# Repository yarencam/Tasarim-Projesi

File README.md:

# Damla Sulama Sistemi Kontrol Kartı
Proje kapsamında, el ile kontrol edilen, bir dizel motor vasıtasıyla sisteme su basan, eski tip **_Damla Sulama Sistemi_** kısmen modernize edilerek arıza ve su kesilmelerinde sistemi durdurarak kullanıcıyı bilgilendirecek yetenekler eklenecektir.

Bitki sulama ve sulamanın otomatik başlatılması için gerekli ölçüm ve kontroller bu projenin kapsamı dışındadır. Bahsi geçen yetenekler sonraki versiyonlarda sisteme eklenebilir.

## Damla Sulama Sistemi
Damla sulama, toprak yüzeyine veya yüzeyin hemen altına yerleştirilen küçük çaplı orifis yardımıyla arıtılmış suyu toprak yüzeyine veya içerisine veren bir sistemdir. Bu sistem suyun belirlenmiş bir desene alçak basınç altında verilmesine imkan sağlar. Bu sistemde su yaygın boru ağı aracılığı ile her bitkiye kadar götürülür. Öte yandan bitkilere verilecek gübreler de sulama suyu ile birlikte verilebilir (fertigation). Kısaca sistemin esası bitkinin ihtiyaç duyduğu su ve besin maddesi miktarını optimum seviyede tutmaktır. Bu yöntem sera, meyve, sebze bahçelerinde en çok kullanılan ve ekonomik su kullanımı sağlayan bir yöntemdir.

Damla sulama sistemleri genellikle aşağıdaki parçalardan oluşur;

* Sisteme su sağlayan basınçlı bir tank
* Tankı doldurmak ve yeterli basıncı sağlamak için bir pompa
* Pompaya hareket sağlamak için bir motor
* Sisteme su sağlamak için bir su kaynağı (su deposu veya sulama kanalı)

## Damla Sulama Sistemlerinde Çozülmesi Amaçlanan Sorun
Bu tip sistemlerde çoğunlukla bir elektrik motoru tercih edilse de eski sistemlerde veya elektrik olmayan bölgelerde halen dizel motor tercih edilmektedir.

Bu tip sistemlerde su soğutmalı pompalar kullanılmaktadır ve pompanın susuz çalıştırılmaması gerekmektedir. Eğer sisteme su sağlayan kaynakta herhangi bir nedenle su olmazsa kısa bir süre sonra pompa aşırı ısınarak yanmaktadır.

Damla sulama sistemlerinde kullanılan basınçlı tankların giriş borusunda bir manometre bulunmaktadır. Kullanıcı bu manometre üzerinde sürekli olarak basınç değerini gözle kontrol etmekte ve basıncın aşırı yükseldiği veya aşırı düştüğü durumlarda sisteme müdahale etmektedir. Bu nedenle sulama yapıldığı süre boyunca bir kişinin sürekli sistemin başında nöbet tutması ve sistemi izlemesi gerekmektedir.

Bu proje tam olarak bu sorunu çözerek hem sistemin otomatik kontrolünü yapmayı ve böylece dikkat dağınıklığı ve ihmalden kaynaklanan hataları gidermeyi hem de bir sistemi izlemekle görevli kişi veya kişilerin başka işlerle uğraşabilmesi için tasarruf sağlanmasını amaçlamaktadır.  

## Kontrol Kartı
Projede problemin çözümü için sistem basıncını izleyen ve aşırı yüksek/aşırı düşük basınç durumlarında sistemi durdurarak kullanıcıyı SMS ile uyaran bir kontrol kartı tasarlanması uygun görülmüştür. Kontrol kartının aşağıdaki görevleri yerine getirmesi beklenmektedir.

* Basınç kontrolü için kullanılan manometrenin yerine veya manometreye ek bir basınç sensörü bağlanarak sistemin basıncı sürekli kontrol edilecektir.
* Farklı marka ve model sistemlerde normal çalışma basınç değeri değişiklik gösterebileceğinden dolayı minimum ve maksimum basınç değerlerinin kullanıcı tarafından belirlenmesi mümkün olmalıdır.
* Sistem basıncı her zaman sabit olmaya bilmektedir. Kısa süreliğine artıp azalarak bir dalgalanma olması normal kabul edilmektedir. Eğer basınç değeri normal aralık dışına çıkarsa, ne kadar süre için bu durumun normal kabul edilmesi gerektiği kullanıcı tarafından belirlenebilmelidir.
* Sistem basıncı normal aralık dışına çıktıktan sonra, kullanıcı tarafından belirlenen süreden daha fazla bu değerlerde kalıyorsa sistemin çalışmasının durdurulması gerekmektedir.
* Sistem herhangi bir nedenle durdurulursa SMS ile kullanıcının bilgilendirilmesi gerekmektedir. Böylece kullanıcı zaman kaybetmeden sorunu gidererek sulamayı tekrar başlatabilir.
* Sistemin SMS yollayacağı telefon numarası kullanıcı tarafından belirlenebilmelidir.
* İlk çalıştırma ve kullanıcının normal çalışma değerleri dışına çıkacak bilinçli olarak yapacağı ayarlar, kontrol kartı tarafından hata durumu olarak algılanacak ve sistemi kapatmaya çalışacaktır. Bu nedenle kartın devre dışı bırakılabilmesi gerekmektedir.

### Kontrol Kartı Blok Diyagramı
Kontrol kartının modüllerini ve yeteneklerini gösteren blok diyagram aşağıdaki gibidir.

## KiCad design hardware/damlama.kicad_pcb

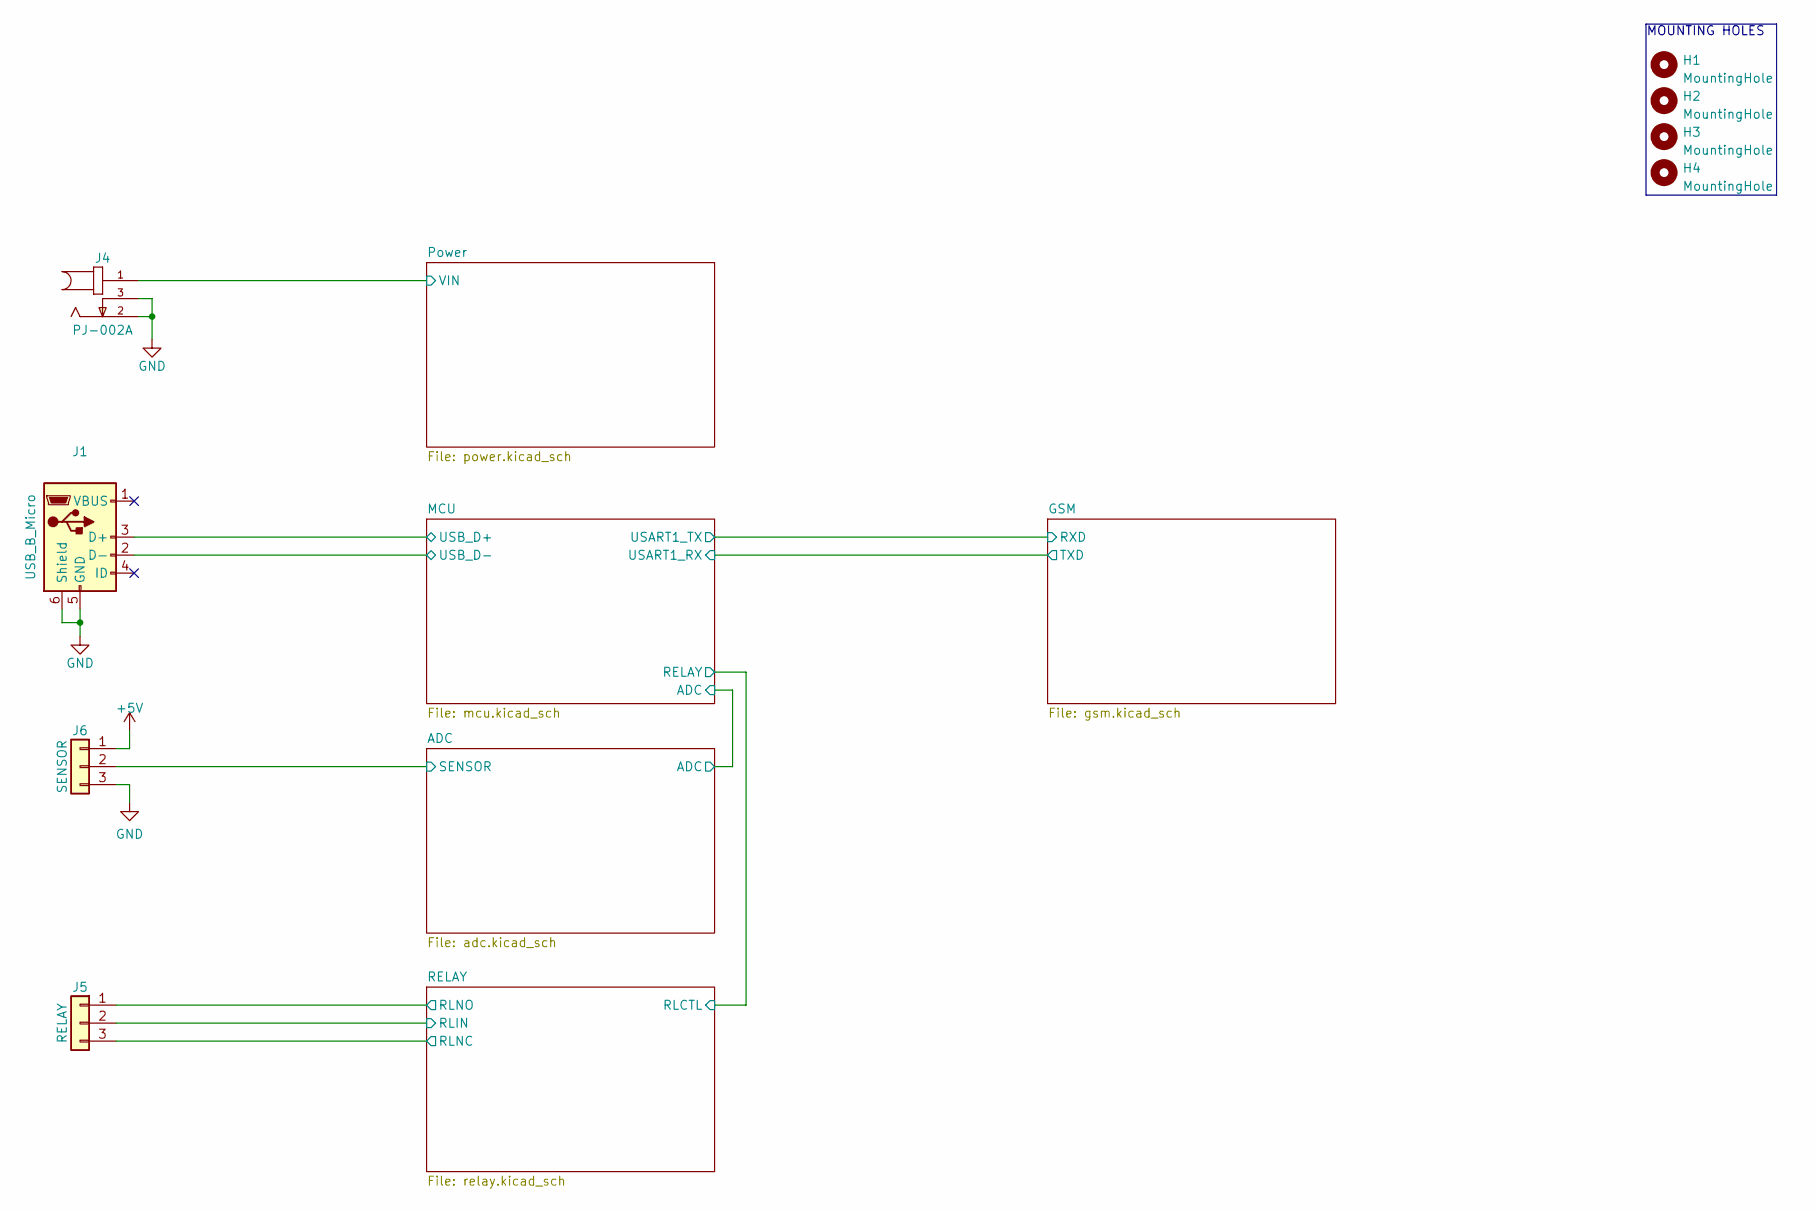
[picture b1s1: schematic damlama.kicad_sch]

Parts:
H1, H2, H3, H4: MountingHole; MountingHole_2.5mm
J1: USB_B_Micro; USB_Micro-B_Molex_47346-0001; DigikeyPN WM11228DKR-ND
J4: PJ-002A; CUI_PJ-002A; DigikeyPN CP-002A-ND
J5: RELAY; PhoenixContact_MSTBA_2,5_3-G-5,08_1x03_P5.08mm_Horizontal
J6: SENSOR; PhoenixContact_MSTBA_2,5_3-G-5,08_1x03_P5.08mm_Horizontal

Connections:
+5V: J6.1; also elsewhere on the board
/ADC/SENSOR: J6.2; also elsewhere on the board
/MCU/USB_D+: J1.3 (D+); also elsewhere on the board
/MCU/USB_D-: J1.2 (D-); also elsewhere on the board
/Power/VIN: J4.1; also elsewhere on the board
/RELAY/RLIN: J5.2; also elsewhere on the board
/RELAY/RLNC: J5.3; also elsewhere on the board
/RELAY/RLNO: J5.1; also elsewhere on the board

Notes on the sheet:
MOUNTING HOLES

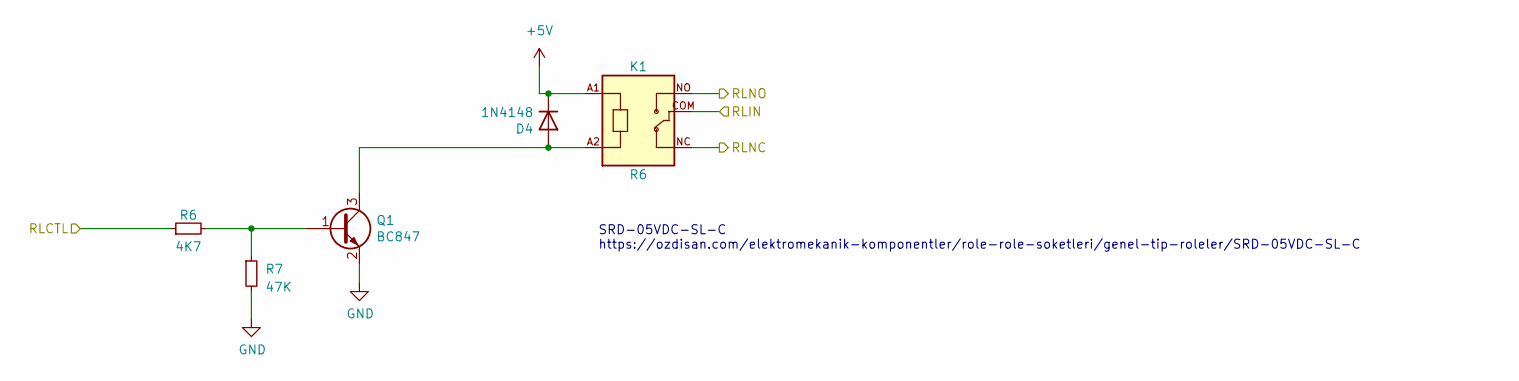
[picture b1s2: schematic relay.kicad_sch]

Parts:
D4: 1N4148; D_MiniMELF; DigikeyPN 1086-15206-ND
K1: R6; RELAY_SRD-05VDC-SL-C
Q1: BC847; SOT-23; DigikeyPN 3757-BC847C_R1_00001DKR-ND
R6: 4K7; R_0603_1608Metric; DigikeyPN 13-RC1206FR-134K7LDKR-ND
R7: 47K; R_0603_1608Metric; DigikeyPN 311-47.0KHRCT-ND

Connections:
+5V: D4.1 (K), K1.A1; also elsewhere on the board
/MCU/RELAY: R6.1; also elsewhere on the board
/RELAY/RLIN: K1.COM; also elsewhere on the board
/RELAY/RLNC: K1.NC; also elsewhere on the board
/RELAY/RLNO: K1.NO; also elsewhere on the board
unnamed: D4.2 (A), K1.A2, Q1.3 (C)
unnamed: Q1.1 (B), R6.2, R7.1

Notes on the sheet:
SRD-05VDC-SL-C https://ozdisan.com/elektromekanik-komponentler/role-role-soketleri/genel-tip-roleler/SRD-05VDC-SL-C

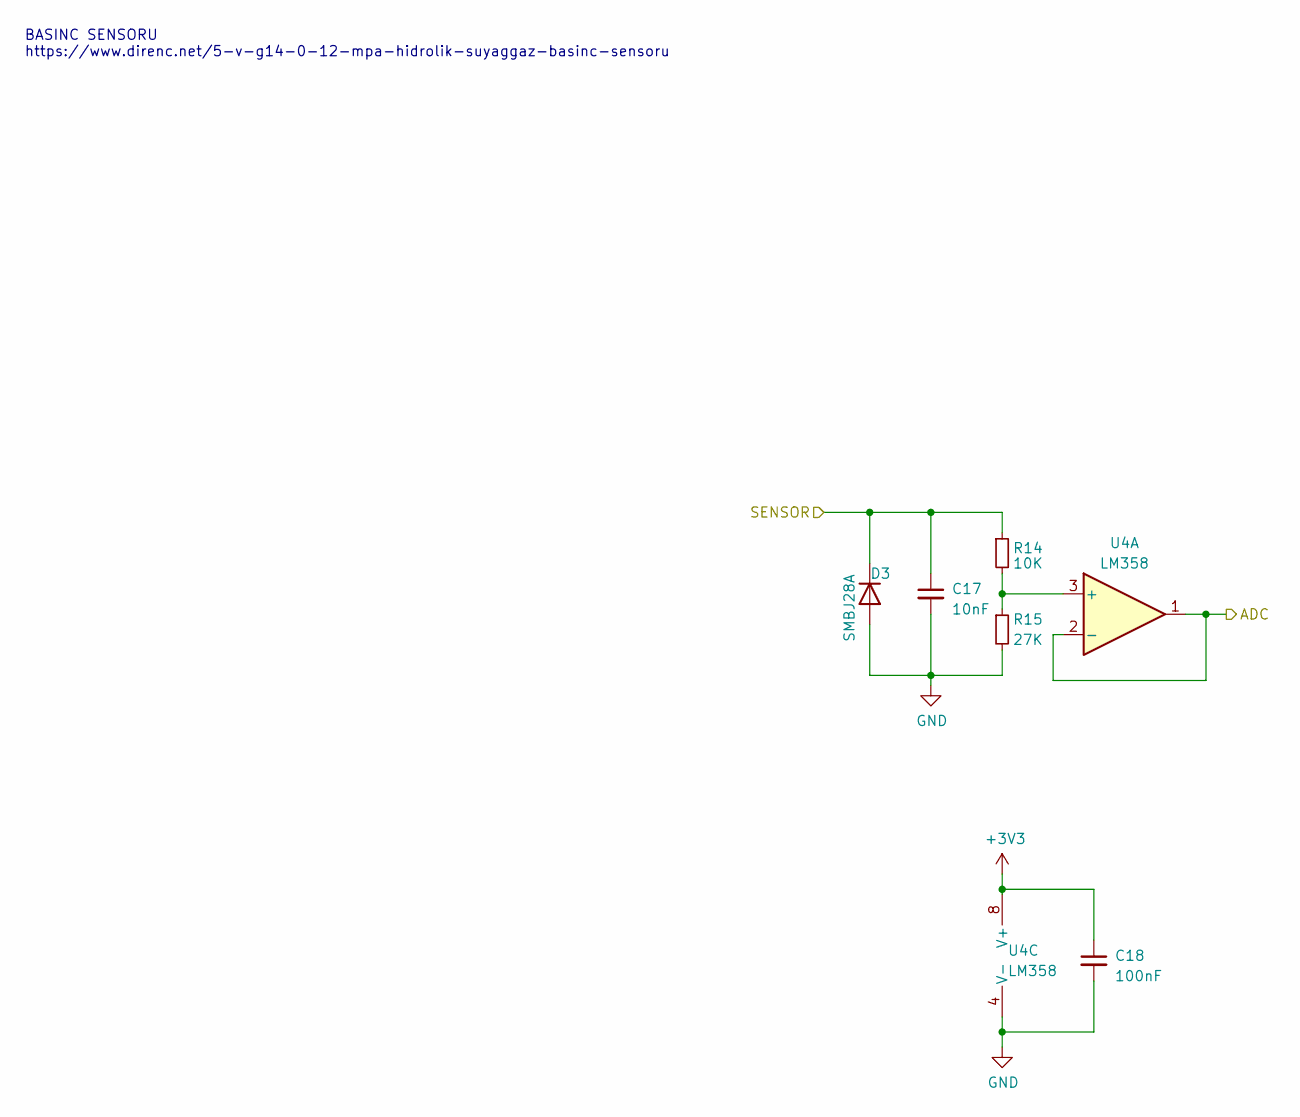
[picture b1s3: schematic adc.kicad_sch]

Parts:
C17: 10nF; C_0603_1608Metric; DigikeyPN 311-1085-6-ND
C18: 100nF; C_0603_1608Metric; DigikeyPN AC0603KPX7R7BB104
D3: SMBJ28A; D_SMB; DigikeyPN SMBJ28ALFDKR-ND
R14: 10K; R_0603_1608Metric; DigikeyPN RNCF0603TKY10K0DKR-ND
R15: 27K; R_0603_1608Metric; DigikeyPN 311-27.0KHRDKR-ND
U4: LM358; SOIC127P599X175-8N; DigikeyPN 296-14601-6-ND

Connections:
/ADC/ADC: U4.1, U4.2 (-); also elsewhere on the board
/ADC/SENSOR: C17.1, D3.1 (K), R14.1; also elsewhere on the board
unnamed: R14.2, R15.1, U4.3 (+)

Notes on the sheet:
BASINC SENSORU https://www.direnc.net/5-v-g14-0-12-mpa-hidrolik-suyaggaz-basinc-sensoru

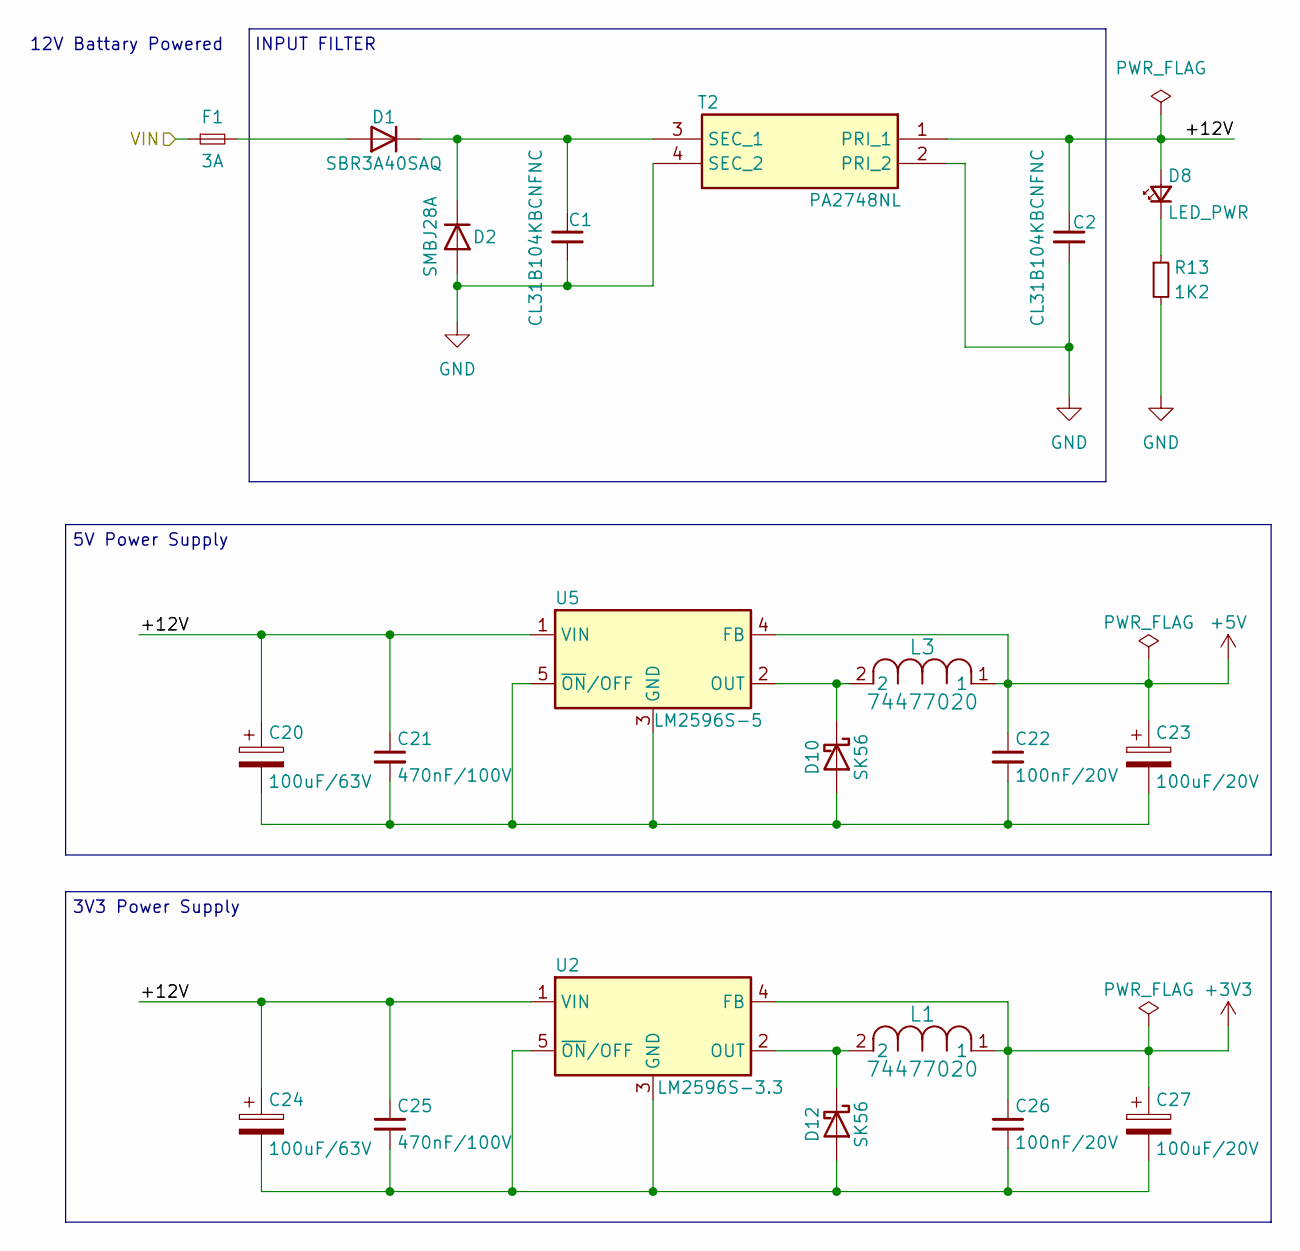
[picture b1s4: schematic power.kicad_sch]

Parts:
C1, C2: CL31B104KBCNFNC; C_1206_3216Metric; DigikeyPN 1276-2744-2-ND
C20, C24: 100uF/63V; CP_Elec_10x10.5; DigikeyPN 399-15648-6-ND
C21, C25: 470nF/100V; C_1206_3216Metric; DigikeyPN 399-C1206C474M1REC7210DKR-ND
C22, C26: 100nF/20V; C_0805_2012Metric; DigikeyPN 718-2500-6-ND
C23, C27: 100uF/20V; CP_Elec_6.3x7.7; DigikeyPN 565-3210-6-ND
D1: SBR3A40SAQ; D_SMA; DigikeyPN SBR3A40SAQ-13DITR-ND
D2: SMBJ28A; D_SMB; DigikeyPN SMBJ28ALFDKR-ND
D8: LED_PWR; LED_D3.0mm; DigikeyPN 1830-1004-ND
D10: SK56; D_SMC; DigikeyPN 1655-SK56DKR-ND
D12: SK56; D_SMC
F1: 3A; Fuse_1206_3216Metric; DigikeyPN P16741DKR-ND
L1, L3: 74477020; IND_1280-WE-PD_WRE; DigikeyPN 732-1235-6-ND
R13: 1K2; R_0603_1608Metric; DigikeyPN 13-RC0603FR-131K2LDKR-ND
T2: PA2748NL; Manufacturer_Part_Number PA2748NL; Mouser Part Number 673-PA2748NL
U2: LM2596S-3.3; TO-263-5_TabPin3; DigikeyPN 4518-LM2596S-3.3DKR-ND
U5: LM2596S-5; TO-263-5_TabPin3; DigikeyPN LM2596S-5.0-ND

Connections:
+5V: C22.1, C23.1, L3.1, U5.4 (FB); also elsewhere on the board
/Power/+12V: C2.1, C20.1, C21.1, C24.1, C25.1, D8.2 (A), T2.1 (PRI_1), U2.1 (VIN), U5.1 (VIN)
/Power/VIN: F1.1; also elsewhere on the board
unnamed: D1.2 (A), F1.2
unnamed: C1.1, D1.1 (K), D2.1 (K), T2.3 (SEC_1)
unnamed: D8.1 (K), R13.1
unnamed: C20.2, C21.2, C22.2, C23.2, D10.2 (A), U5.3 (GND), U5.5 (~ON/OFF)
unnamed: D10.1 (K), L3.2, U5.2 (OUT)
unnamed: C24.2, C25.2, C26.2, C27.2, D12.2 (A), U2.3 (GND), U2.5 (~ON/OFF)
unnamed: D12.1 (K), L1.2, U2.2 (OUT)

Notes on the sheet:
5V Power Supply
INPUT FILTER
12V Battary Powered
3V3 Power Supply

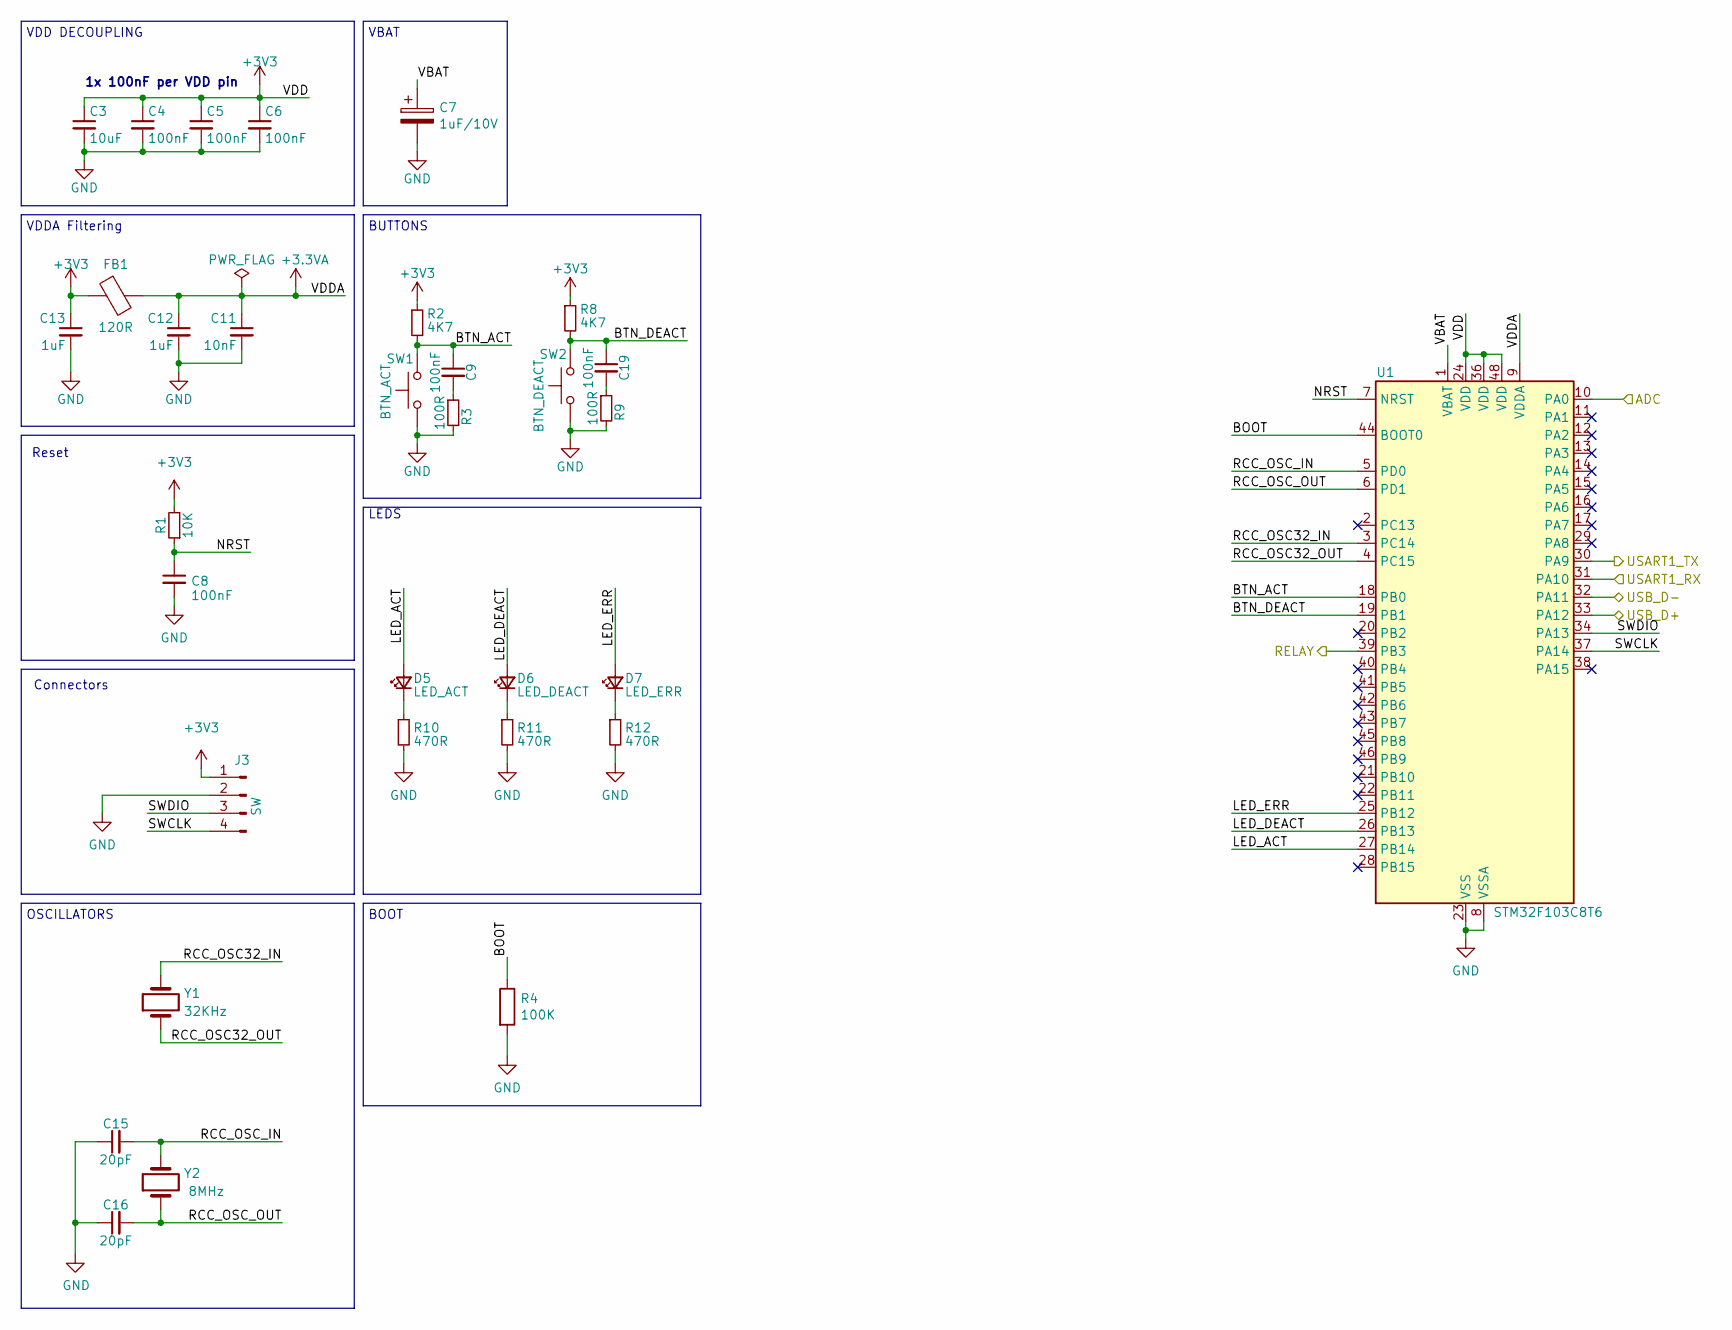
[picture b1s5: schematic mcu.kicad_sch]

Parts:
C3: 10uF; C_0603_1608Metric; DigikeyPN 13-CC0603MPX5R5BB106DKR-ND
C4, C5, C6, C8, C9, C19: 100nF; C_0603_1608Metric; DigikeyPN AC0603KPX7R7BB104
C7: 1uF/10V; C_0603_1608Metric; DigikeyPN 478-12231-6-ND
C11: 10nF; C_0603_1608Metric; DigikeyPN 13-CC0100KRX5R4BB103TR-ND
C12, C13: 1uF; C_0603_1608Metric; DigikeyPN 311-1447-6-ND
C15, C16: 20pF; C_0603_1608Metric; DigikeyPN 399-C0603C200G8HAC7867DKR-ND
D5: LED_ACT; LED_D3.0mm; DigikeyPN 1830-1004-ND
D6: LED_DEACT; LED_D3.0mm; DigikeyPN 1830-1001-ND
D7: LED_ERR; LED_D3.0mm; DigikeyPN 1830-1000-ND
FB1: 120R; L_0603_1608Metric; DigikeyPN 732-4665-6-ND
J3: SW; PinHeader_1x04_P2.54mm_Vertical
R1: 10K; R_0603_1608Metric; DigikeyPN RNCP0603FTD10K0DKR-ND
R2, R8: 4K7; R_0603_1608Metric; DigikeyPN 13-RC1206FR-134K7LDKR-ND
R3, R9: 100R; R_0603_1608Metric; DigikeyPN RR08P100DDKR-ND
R4: 100K; R_0603_1608Metric; Digikey 311-100KHRDKR-ND
R10, R11, R12: 470R; R_0603_1608Metric; DigikeyPN 1292-WR06X471JTLDKR-ND
SW1: BTN_ACT; SW_Push_1P1T_NO_Vertical_Wuerth_434133025816; DigikeyPN 732-13663-6-ND
SW2: BTN_DEACT; SW_Push_1P1T_NO_Vertical_Wuerth_434133025816; DigikeyPN 732-13663-6-ND
U1: STM32F103C8T6; LQFP-48_7x7mm_P0.5mm; DigikeyPN 497-6063-ND
Y1: 32KHz; Crystal_C38-LF_D3.0mm_L8.0mm_Vertical; DigikeyPN X1123-ND
Y2: 8MHz; Crystal_SMD_HC49-SD; DigikeyPN 631-1010-6-ND

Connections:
+3.3VA: C11.1, C12.1, FB1.2, U1.9 (VDDA)
/ADC/ADC: U1.10 (PA0); also elsewhere on the board
/GSM/RXD: U1.30 (PA9); also elsewhere on the board
/GSM/TXD: U1.31 (PA10); also elsewhere on the board
/MCU/BTN_ACT: C9.1, R2.2, SW1.2, U1.18 (PB0)
/MCU/LED_ACT: D5.2 (A), U1.27 (PB14)
/MCU/LED_DEACT: D6.2 (A), U1.26 (PB13)
/MCU/LED_ERR: D7.2 (A), U1.25 (PB12)
/MCU/NRST: C8.1, R1.1, U1.7 (NRST)
/MCU/RCC_OSC32_IN: U1.3 (PC14), Y1.2
/MCU/RCC_OSC32_OUT: U1.4 (PC15), Y1.1
/MCU/RCC_OSC_IN: C15.2, U1.5 (PD0), Y2.2
/MCU/RCC_OSC_OUT: C16.2, U1.6 (PD1), Y2.1
/MCU/RELAY: U1.39 (PB3); also elsewhere on the board
/MCU/SWCLK: J3.4, U1.37 (PA14)
/MCU/SWDIO: J3.3, U1.34 (PA13)
/MCU/USB_D+: U1.33 (PA12); also elsewhere on the board
/MCU/USB_D-: U1.32 (PA11); also elsewhere on the board
/MCU/VBAT: C7.1, U1.1 (VBAT)
unnamed: C9.2, R3.1
unnamed: C19.2, R9.1
unnamed: D5.1 (K), R10.1
unnamed: D6.1 (K), R11.1
unnamed: D7.1 (K), R12.1

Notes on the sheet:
1x 100nF per VDD pin
VDD DECOUPLING
BUTTONS
LEDS
BOOT
VBAT
Reset
OSCILLATORS
VDDA Filtering
Connectors

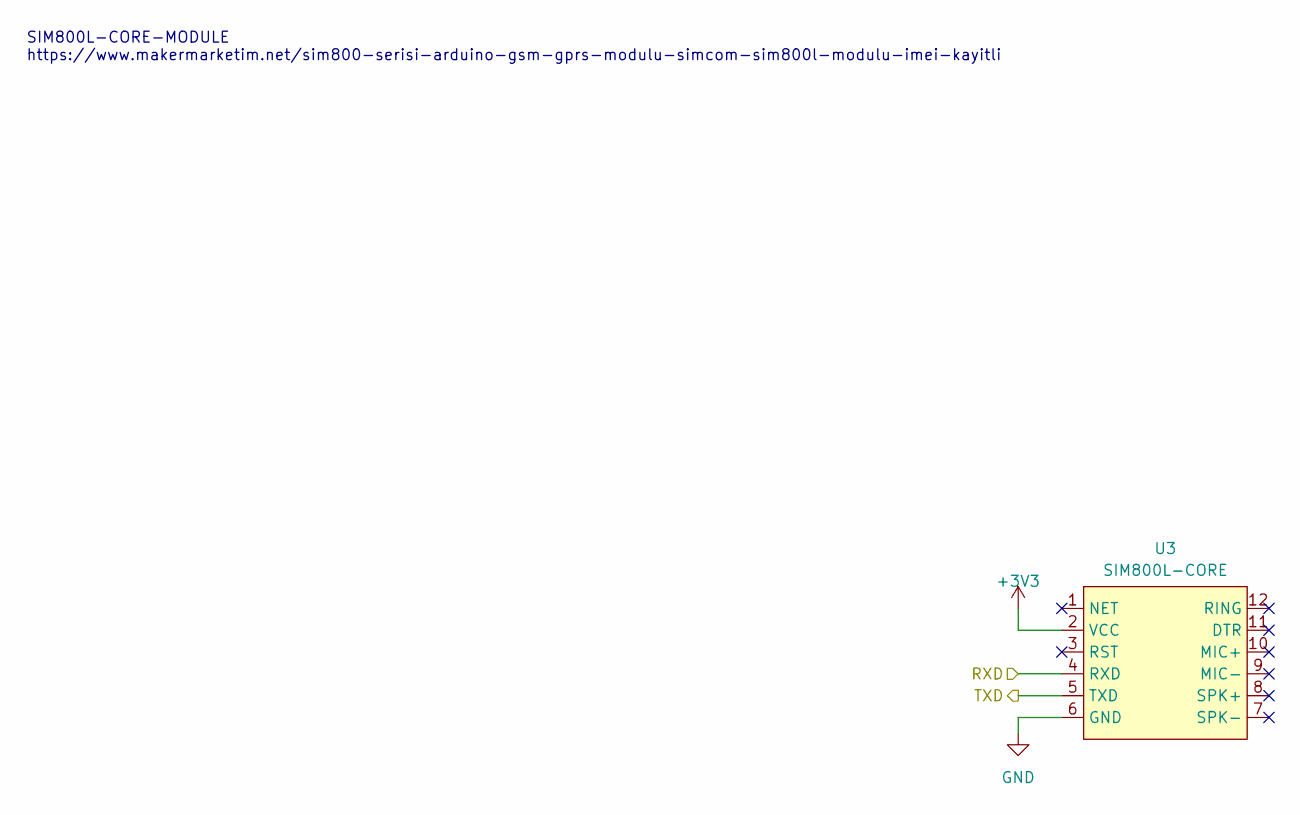
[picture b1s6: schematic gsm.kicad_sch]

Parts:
U3: SIM800L-CORE

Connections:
/GSM/RXD: U3.4 (RXD); also elsewhere on the board
/GSM/TXD: U3.5 (TXD); also elsewhere on the board

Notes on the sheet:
SIM800L-CORE-MODULE https://www.makermarketim.net/sim800-serisi-arduino-gsm-gprs-modulu-simcom-sim800l-modulu-imei-kayitli

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
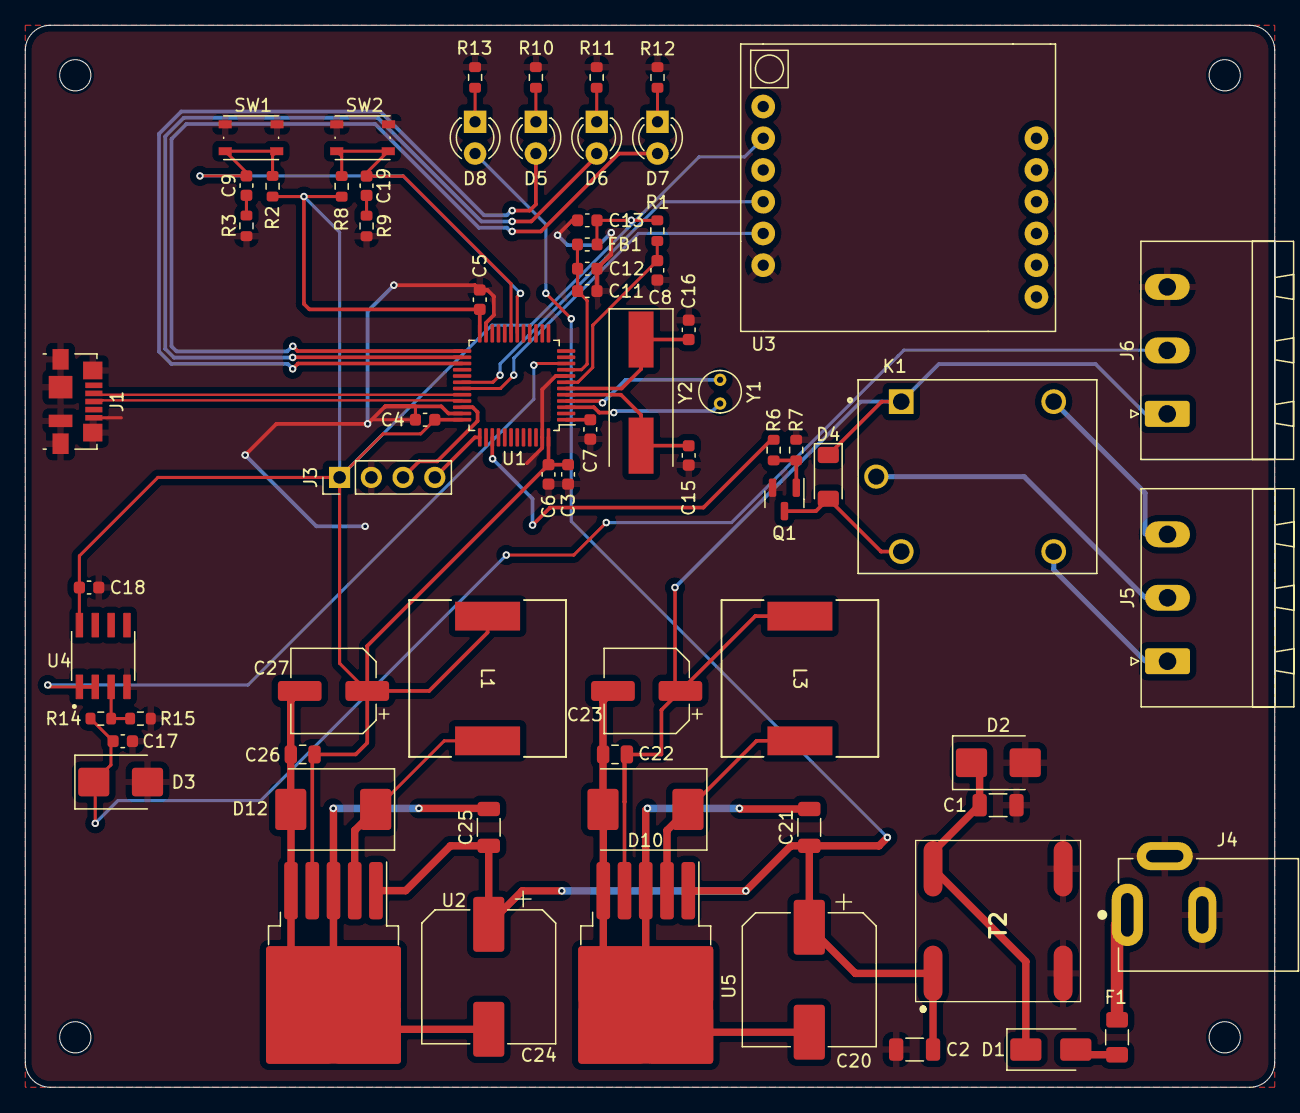
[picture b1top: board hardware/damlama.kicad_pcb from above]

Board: 2 copper layers, 100.0 x 85.0 mm, 73 parts (0 on the bottom side), 44 nets.

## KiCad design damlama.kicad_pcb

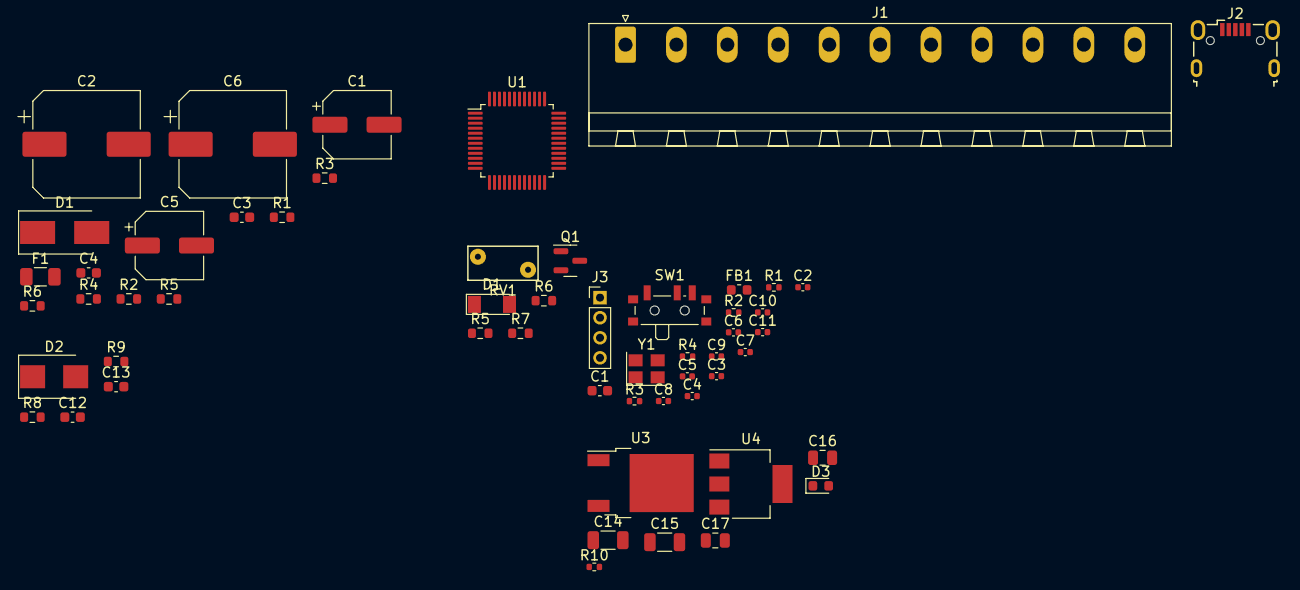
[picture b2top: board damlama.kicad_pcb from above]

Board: 2 copper layers, 55 parts (0 on the bottom side), 29 nets, no tracks yet.

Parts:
C1: 10uF/10V; CP_Elec_6.3x7.7
C1#2: 10u; C_0603_1608Metric
C2, C6#2: 100uF/35V; CP_Elec_10x10.5
C2#2, C3, C5, C6, C8: 100n; C_0402_1005Metric
C3#2, C4, C12: 10nF; C_0603_1608Metric
C4#2, C7: 10p; C_0402_1005Metric
C5#2: 10uF/35V; CP_Elec_6.3x7.7
C9: 10n; C_0402_1005Metric
C10, C11: 1u; C_0402_1005Metric
C13: 100nF; C_0603_1608Metric
C14, C15: 10uF; C_1206_3216Metric
C16, C17: 22u; C_0805_2012Metric
D1: SBR3A40SAQ; D_SMB_Handsoldering
D1#2: 1N4148; D_MiniMELF
D2: SMBJ28A; D_SMB
D3: RED; LED_0603_1608Metric
F1: 1A; Fuse_1206_3216Metric
FB1: 120R; L_0603_1608Metric
J1: Conn_01x11_Male; PhoenixContact_MSTBA_2,5_11-G-5,08_1x11_P5.08mm_Horizontal
J2: USB_B_Micro; USB_Micro-B_Wuerth_629105150521
J3: Conn_01x04_Male; PinHeader_1x04_P2.00mm_Vertical
Q1: BC847; SOT-23
R1, R2#2, R4, R10: 1k5; R_0402_1005Metric
R1#2: 470; R_0603_1608Metric
R2: 18K; R_0603_1608Metric
R3: 10K; R_0603_1608Metric
R3#2: 10k; R_0402_1005Metric
R4#2: 1K; R_0603_1608Metric
R5, R7: 4K7; R_0603_1608Metric
R5#2: 33; R_0603_1608Metric
R6: 120; R_0603_1608Metric
R6#2: 47K; R_0603_1608Metric
R8: 150; R_0603_1608Metric
R9: 15; R_0603_1608Metric
RV1: Varistor; RV_Disc_D7mm_W3.4mm_P5mm
SW1: SW_SPDT; SW_SPDT_PCM12
U1: STM32F103C8Tx; LQFP-48_7x7mm_P0.5mm
U3: LD1086DT50TR; TO-252-2
U4: AMS1117-3.3; SOT-223-3_TabPin2
Y1: 16MHz; Crystal_SMD_3225-4Pin_3.2x2.5mm

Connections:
+3.3V: C1#2.1, C2#2.1, C5.1, C6.1, C8.1, C11.1, C17.1, D3.2 (A), FB1.1, J3.1, R1.1, R2#2.1, R4.1, SW1.3 (C), U1.1 (VBAT), U1.24 (VDD), U1.36 (VDD), U1.48 (VDD), U4.2 (VO)
+3.3VA: C9.1, C10.1, FB1.2, U1.9 (VDDA)
+3V3: C1.1, C3#2.1, C13.1, R1#2.1, R2.1
+5V: C15.1, C16.1, U3.2 (OUT), U4.3 (VI)
+12V: C5#2.1, C6#2.1, D1#2.1 (K), R6.1
/ADC/SENS-: C12.1, D2.1 (K), R8.1
/MCU/HSE_IN: C4#2.1, U1.5 (PD0), Y1.1
/MCU/HSE_OUT: C7.1, U1.6 (PD1), Y1.3
/MCU/I2C2_SCL: J1.5, R1.2, U1.21 (PB10)
/MCU/I2C2_SDA: J1.6, R2#2.2, U1.22 (PB11)
/MCU/NRST: C3.1, U1.7 (NRST)
/MCU/SWCLK: J3.3, U1.37 (PA14)
/MCU/SWDI0: J3.2, U1.34 (PA13)
/MCU/SW_BOOT0: R3#2.1, SW1.2 (B)
/MCU/USART1_RX: J1.4, U1.43 (PB7)
/MCU/USART1_TX: J1.3, U1.42 (PB6)
/MCU/USB_D+: J2.3 (D+), R4.2, U1.33 (PA12)
/MCU/USB_D-: J2.2 (D-), U1.32 (PA11)
/Power/PWR_LED_K: D3.1 (K), R10.1
GND: C1.2, C1#2.2, C2.2, C2#2.2, C3.2, C4.2, C4#2.2, C5.2, C5#2.2, C6.2, C6#2.2, C7.2, C8.2, C9.2, C10.2, C11.2, C12.2, C13.2, C14.2, C15.2, C16.2, C17.2, D2.2 (A), J1.2, J2.5 (GND), J3.4, Q1.2 (E), R3.2, R5#2.2, R6#2.2, R9.2, R10.2, SW1.1 (A), U1.8 (VSSA), U1.23 (VSS), U1.35 (VSS), U1.47 (VSS), U3.1 (ADJ/GND), U4.1 (GND), Y1.2, Y1.4
unnamed: C2.1, D1.1 (K)
unnamed: C3#2.2, R2.2, R3.1
unnamed: D1.2 (A), D1#2.2 (A), F1.1, Q1.3 (C), R7.2
unnamed: Q1.1 (B), R5.1, R6#2.1
unnamed: R3#2.2, U1.44 (BOOT0)
unnamed: R4#2.1, R6.2
unnamed: R4#2.2, R5#2.1
unnamed: R8.2, R9.1
VCC: C14.1, F1.2, J1.1, U3.3 (IN)

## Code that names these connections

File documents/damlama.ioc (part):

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Mcu.Name=STM32F103C(8-B)Tx
Mcu.Package=LQFP48
Mcu.UserName=STM32F103C8Tx
PA0-WKUP.GPIOParameters=GPIO_Label
PA0-WKUP.GPIO_Label=ADC
PA0-WKUP.Signal=ADCx_IN0
PA10.Mode=Asynchronous
PA10.Signal=USART1_RX
PA11.Mode=Device
PA11.Signal=USB_DM
PA12.Mode=Device
PA12.Signal=USB_DP
PA13.Mode=Serial_Wire
PA13.Signal=SYS_JTMS-SWDIO
PA14.Mode=Serial_Wire
PA14.Signal=SYS_JTCK-SWCLK
PA9.Mode=Asynchronous
PA9.Signal=USART1_TX
PB0.GPIOParameters=GPIO_Label
PB0.GPIO_Label=BTN_ACTIVATE
PB0.Signal=GPXTI0
PB1.GPIOParameters=GPIO_Label
PB1.GPIO_Label=BTN_DEACTIVATE
PB1.Signal=GPXTI1
PB12.GPIOParameters=GPIO_Label
PB12.GPIO_Label=LED_ERR
PB12.Signal=GPIO_Output
PB13.GPIOParameters=GPIO_Label
PB13.GPIO_Label=LED_DEACT
PB13.Signal=GPIO_Output
PB14.GPIOParameters=GPIO_Label
PB14.GPIO_Label=LED_ACT
PB14.Signal=GPIO_Output
PB3.GPIOParameters=GPIO_Label
PB3.GPIO_Label=RELAY
PB3.Signal=GPIO_Output
PC14-OSC32_IN.Mode=LSE-External-Oscillator
PC14-OSC32_IN.Signal=RCC_OSC32_IN
PC15-OSC32_OUT.Mode=LSE-External-Oscillator
PC15-OSC32_OUT.Signal=RCC_OSC32_OUT
PD0-OSC_IN.Mode=HSE-External-Oscillator
PD0-OSC_IN.Signal=RCC_OSC_IN
PD1-OSC_OUT.Mode=HSE-External-Oscillator
PD1-OSC_OUT.Signal=RCC_OSC_OUT
RCC.SYSCLKFreq_VALUE=48000000
RCC.SYSCLKSource=RCC_SYSCLKSOURCE_PLLCLK
board=custom

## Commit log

2022-11-19 * File structure fixed * gitignore file added
2022-11-19 * Project fixed
2022-11-29 Directory structure fixed.
2022-11-29 README.md moved to root
2023-04-03 Update PCB
2023-04-29 README modified
2023-04-30 Beta Finished
2023-04-30 Block diagram fixed
2023-05-06 MCU BOOT0 mistake fixed
2023-06-21 Firmware added
